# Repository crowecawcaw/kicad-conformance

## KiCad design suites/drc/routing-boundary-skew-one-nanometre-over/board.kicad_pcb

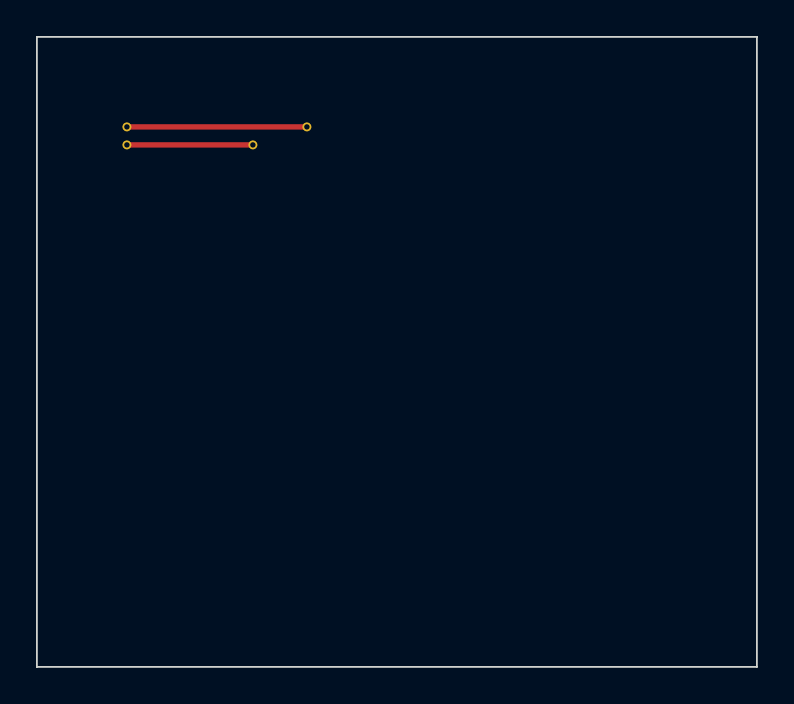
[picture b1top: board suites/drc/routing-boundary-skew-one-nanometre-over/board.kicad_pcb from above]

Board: 2 copper layers, 40.0 x 35.0 mm, 4 parts (0 on the bottom side), 2 nets.

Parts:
PAIR_NA: TestPad
PAIR_NB: TestPad
PAIR_PA: TestPad
PAIR_PB: TestPad

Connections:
PAIR_N: PAIR_NA.1, PAIR_NB.1
PAIR_P: PAIR_PA.1, PAIR_PB.1

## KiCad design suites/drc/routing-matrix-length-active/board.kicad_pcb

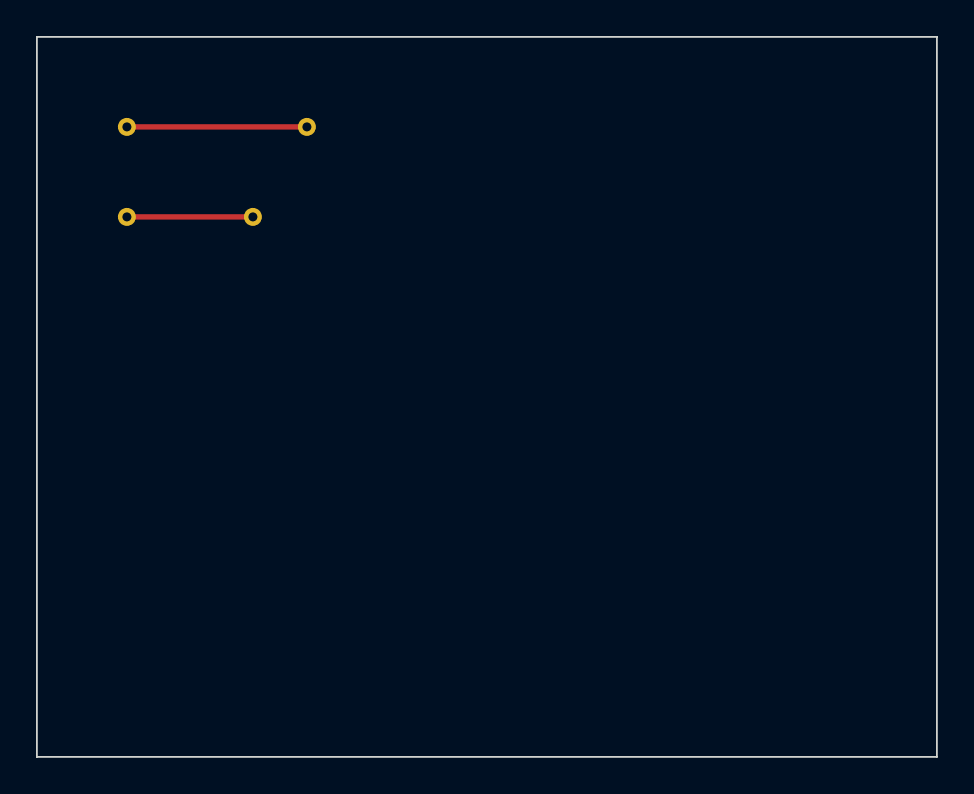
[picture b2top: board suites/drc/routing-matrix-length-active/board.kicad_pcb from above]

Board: 2 copper layers, 50.0 x 40.0 mm, 4 parts (0 on the bottom side), 2 nets.

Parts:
LONGA: TestPad
LONGB: TestPad
SHORTA: TestPad
SHORTB: TestPad

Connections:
LONG: LONGA.1, LONGB.1
SHORT: SHORTA.1, SHORTB.1
